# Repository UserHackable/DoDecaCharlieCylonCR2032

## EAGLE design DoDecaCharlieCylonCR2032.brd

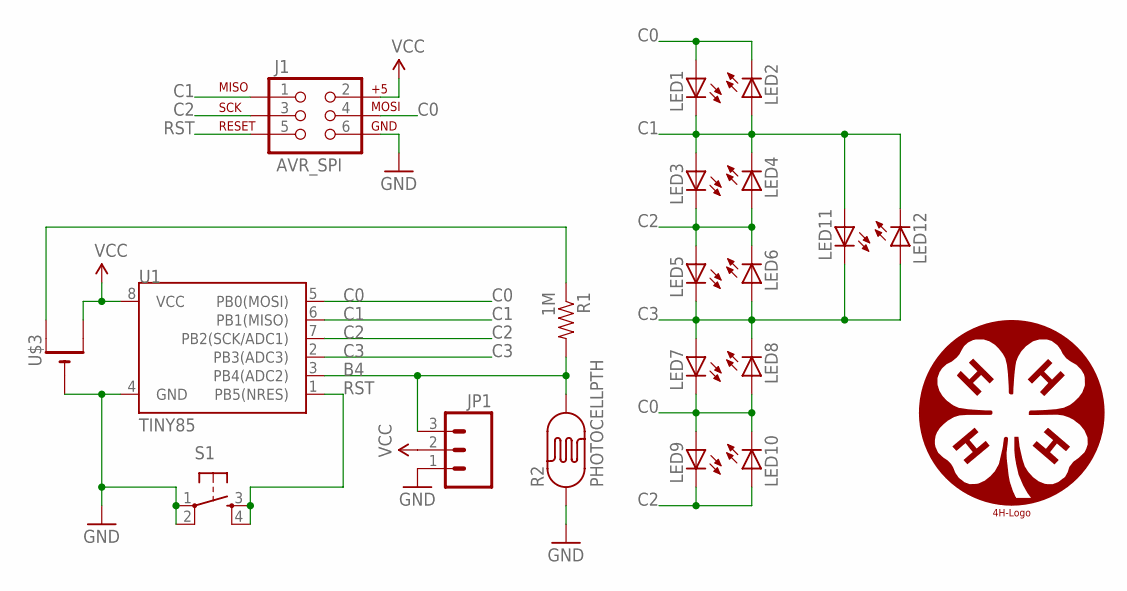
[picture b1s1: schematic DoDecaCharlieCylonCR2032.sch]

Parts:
J1: AVR_SPI; 2X3-NS
JP1: M03PTH; 1X03
LED1, LED2, LED3, LED4, LED5, LED6, LED7, LED8, LED9, LED10, LED11, LED12: LEDOVAL; LED-OVAL
R1: 1M; AXIAL-0.3
R2: PHOTOCELLPTH; PHOTOCELL
S1: TAC_SWITCHPTH; TACTILE-PTH
U1: TINY85; DIP08
U$1: 4H-LOGO6; 4H_LOGO_6
U$3: CR2032THM; CR2032-THRU

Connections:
B4: JP1.3, R1.P$2 (2), R2.2, U1.3 (PB4(ADC2))
C0: J1.4 (MOSI), LED1.ANODE (A), LED2.CATHODE (C), LED7.CATHODE (C), LED8.ANODE (A), LED9.ANODE (A), LED10.CATHODE (C), U1.5 (PB0(MOSI))
C1: J1.1 (MISO), LED1.CATHODE (C), LED2.ANODE (A), LED3.ANODE (A), LED4.CATHODE (C), LED11.ANODE (A), LED12.CATHODE (C), U1.6 (PB1(MISO))
C2: J1.3 (SCK), LED3.CATHODE (C), LED4.ANODE (A), LED5.ANODE (A), LED6.CATHODE (C), LED9.CATHODE (C), LED10.ANODE (A), U1.7 (PB2(SCK/ADC1))
C3: LED5.CATHODE (C), LED6.ANODE (A), LED7.ANODE (A), LED8.CATHODE (C), LED11.CATHODE (C), LED12.ANODE (A), U1.2 (PB3(ADC3))
GND: J1.6 (GND), JP1.1, R2.1, S1.1, S1.2, U1.4 (GND), U$3.-
unnamed: R1.P$1 (1), U$3.+1 (+)
RST: J1.5 (RST), S1.3, S1.4, U1.1 (PB5(NRES))
VCC: J1.2 (V+), JP1.2, U1.8 (VCC), U$3.+2 (+1)

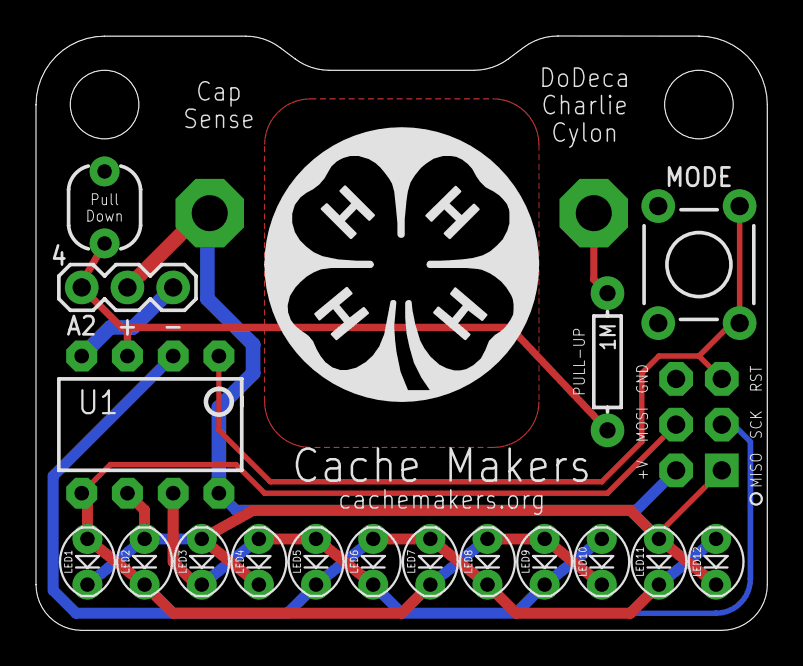
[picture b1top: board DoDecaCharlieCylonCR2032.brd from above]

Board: 2 copper layers, 40.6 x 33.0 mm, 20 parts (1 on the bottom side), 9 nets.

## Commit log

2016-04-06 updating makefile
2016-04-06 changing logo
2016-04-06 update battery holder
2016-04-06 updating images
2016-04-06 updating battery holder
2016-04-07 changing branding
2016-04-07 updating logo
2016-04-07 updating branding
2016-04-07 updating schematic
2016-04-07 from Makefile

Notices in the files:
parts and their libraries:
SparkFun-DigitalIC: Licensing: Creative Commons ShareAlike 4.0 International - https://creativecommons.org/licenses/by-sa/4.0
